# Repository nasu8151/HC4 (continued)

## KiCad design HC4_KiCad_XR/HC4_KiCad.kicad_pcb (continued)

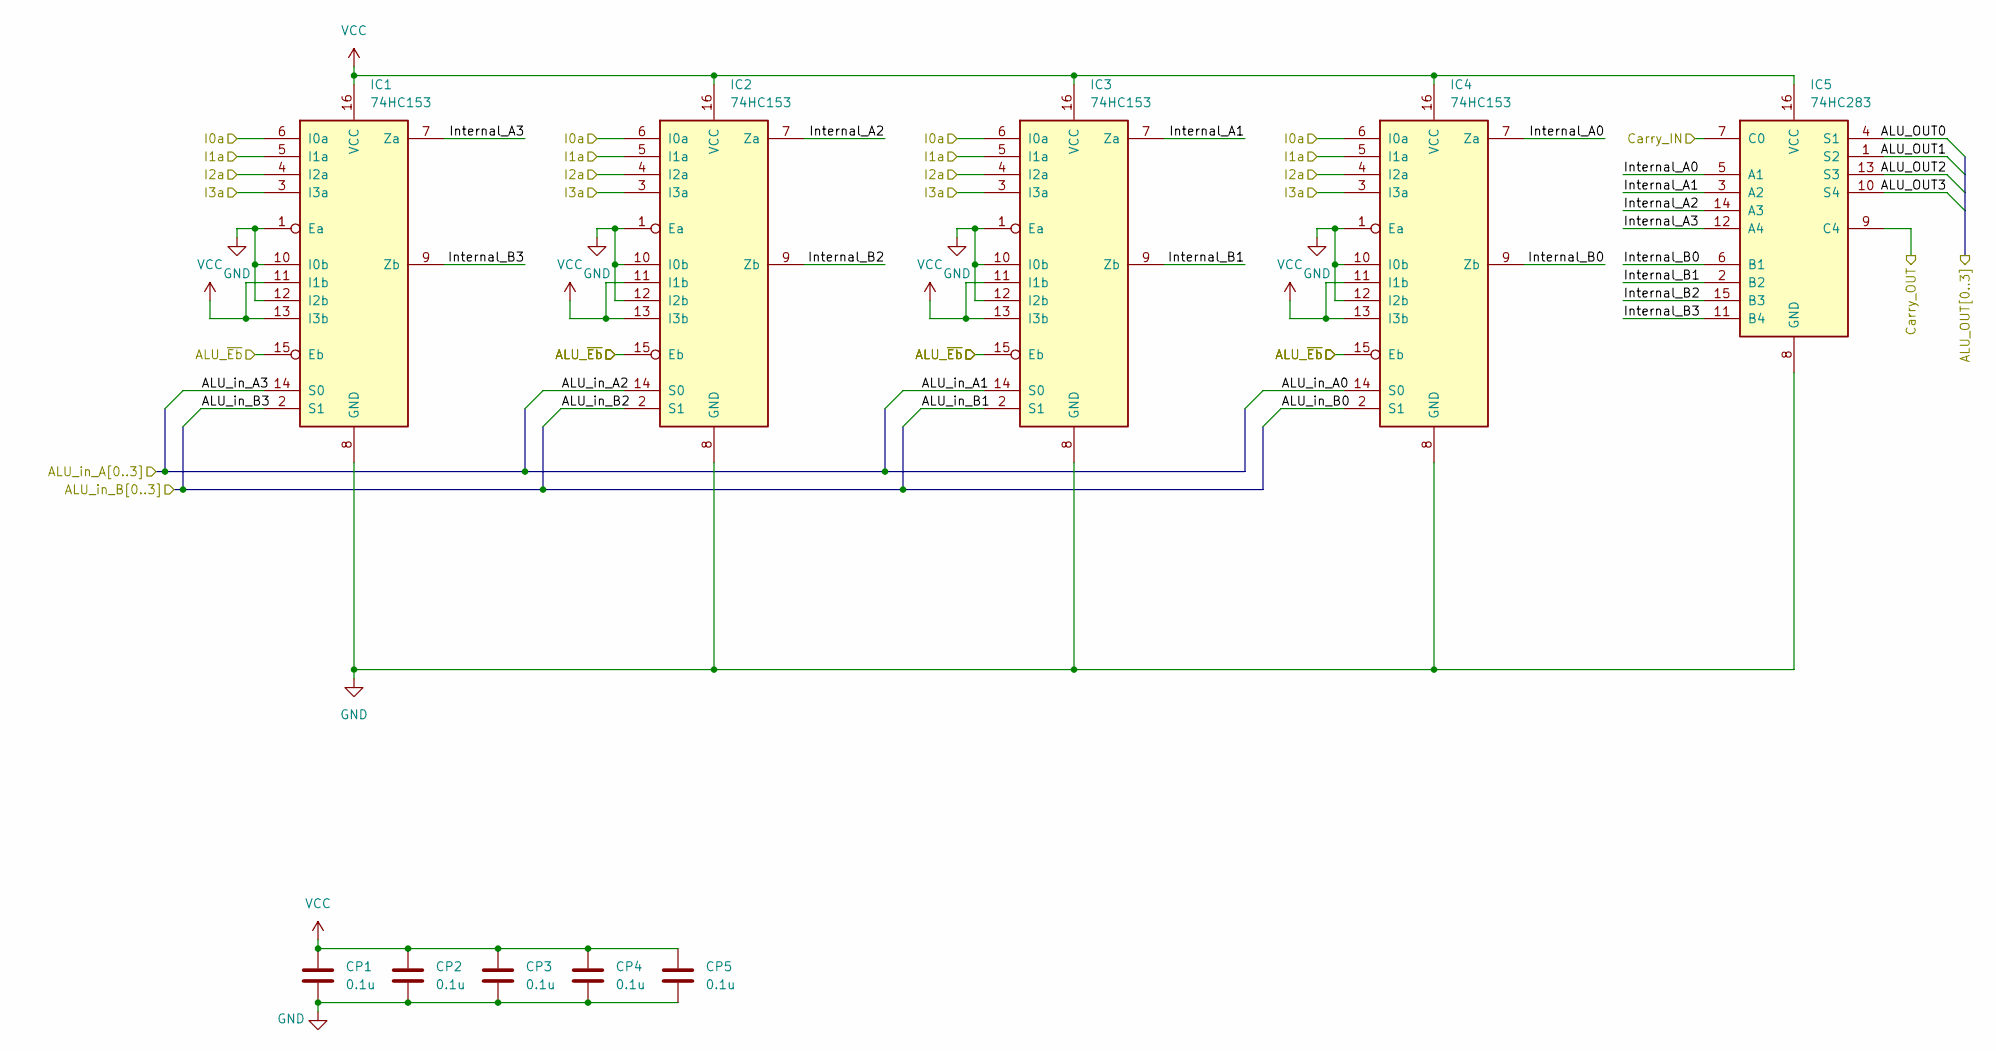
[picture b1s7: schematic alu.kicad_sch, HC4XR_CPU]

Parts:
CP1, CP2, CP3, CP4, CP5: 0.1u; C_0603_1608Metric
IC1, IC2, IC3, IC4: 74HC153; DIP-16_W7.62mm
IC5: 74HC283; DIP-16_W7.62mm

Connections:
/ALU/ALU_OUT0: IC5.4 (S1); also elsewhere on the board
/ALU/ALU_OUT1: IC5.1 (S2); also elsewhere on the board
/ALU/ALU_OUT2: IC5.13 (S3); also elsewhere on the board
/ALU/ALU_OUT3: IC5.10 (S4); also elsewhere on the board
/ALU/ALU_in_A0: IC4.14 (S0); also elsewhere on the board
/ALU/ALU_in_A1: IC3.14 (S0); also elsewhere on the board
/ALU/ALU_in_A2: IC2.14 (S0); also elsewhere on the board
/ALU/ALU_in_A3: IC1.14 (S0); also elsewhere on the board
/ALU/ALU_in_B0: IC4.2 (S1); also elsewhere on the board
/ALU/ALU_in_B1: IC3.2 (S1); also elsewhere on the board
/ALU/ALU_in_B2: IC2.2 (S1); also elsewhere on the board
/ALU/ALU_in_B3: IC1.2 (S1); also elsewhere on the board
/ALU/Carry_OUT: IC5.9 (C4); also elsewhere on the board
/ALU/I0a: IC1.6 (I0a), IC2.6 (I0a), IC3.6 (I0a), IC4.6 (I0a); also elsewhere on the board
/ALU/I1a: IC1.5 (I1a), IC2.5 (I1a), IC3.5 (I1a), IC4.5 (I1a); also elsewhere on the board
/ALU/I2a: IC1.4 (I2a), IC2.4 (I2a), IC3.4 (I2a), IC4.4 (I2a); also elsewhere on the board
/ALU/I3a: IC1.3 (I3a), IC2.3 (I3a), IC3.3 (I3a), IC4.3 (I3a); also elsewhere on the board
/ALU/Internal_A0: IC4.7 (Za), IC5.5 (A1)
/ALU/Internal_A1: IC3.7 (Za), IC5.3 (A2)
/ALU/Internal_A2: IC2.7 (Za), IC5.14 (A3)
/ALU/Internal_A3: IC1.7 (Za), IC5.12 (A4)
/ALU/Internal_B0: IC4.9 (Zb), IC5.6 (B1)
/ALU/Internal_B1: IC3.9 (Zb), IC5.2 (B2)
/ALU/Internal_B2: IC2.9 (Zb), IC5.15 (B3)
/ALU/Internal_B3: IC1.9 (Zb), IC5.11 (B4)
/Instruction Decoder/Carry_Flg: IC5.7 (C0); also elsewhere on the board
/Instruction Decoder/~Carry_EN: IC1.15 (Eb), IC2.15 (Eb), IC3.15 (Eb), IC4.15 (Eb); also elsewhere on the board
GND: CP1.2, CP2.2, CP3.2, CP4.2, CP5.2, IC1.1 (Ea), IC1.8 (GND), IC1.10 (I0b), IC1.12 (I2b), IC2.1 (Ea), IC2.8 (GND), IC2.10 (I0b), IC2.12 (I2b), IC3.1 (Ea), IC3.8 (GND), IC3.10 (I0b), IC3.12 (I2b), IC4.1 (Ea), IC4.8 (GND), IC4.10 (I0b), IC4.12 (I2b), IC5.8 (GND); also elsewhere on the board
VCC: CP1.1, CP2.1, CP3.1, CP4.1, CP5.1, IC1.11 (I1b), IC1.13 (I3b), IC1.16 (VCC), IC2.11 (I1b), IC2.13 (I3b), IC2.16 (VCC), IC3.11 (I1b), IC3.13 (I3b), IC3.16 (VCC), IC4.11 (I1b), IC4.13 (I3b), IC4.16 (VCC), IC5.16 (VCC); also elsewhere on the board

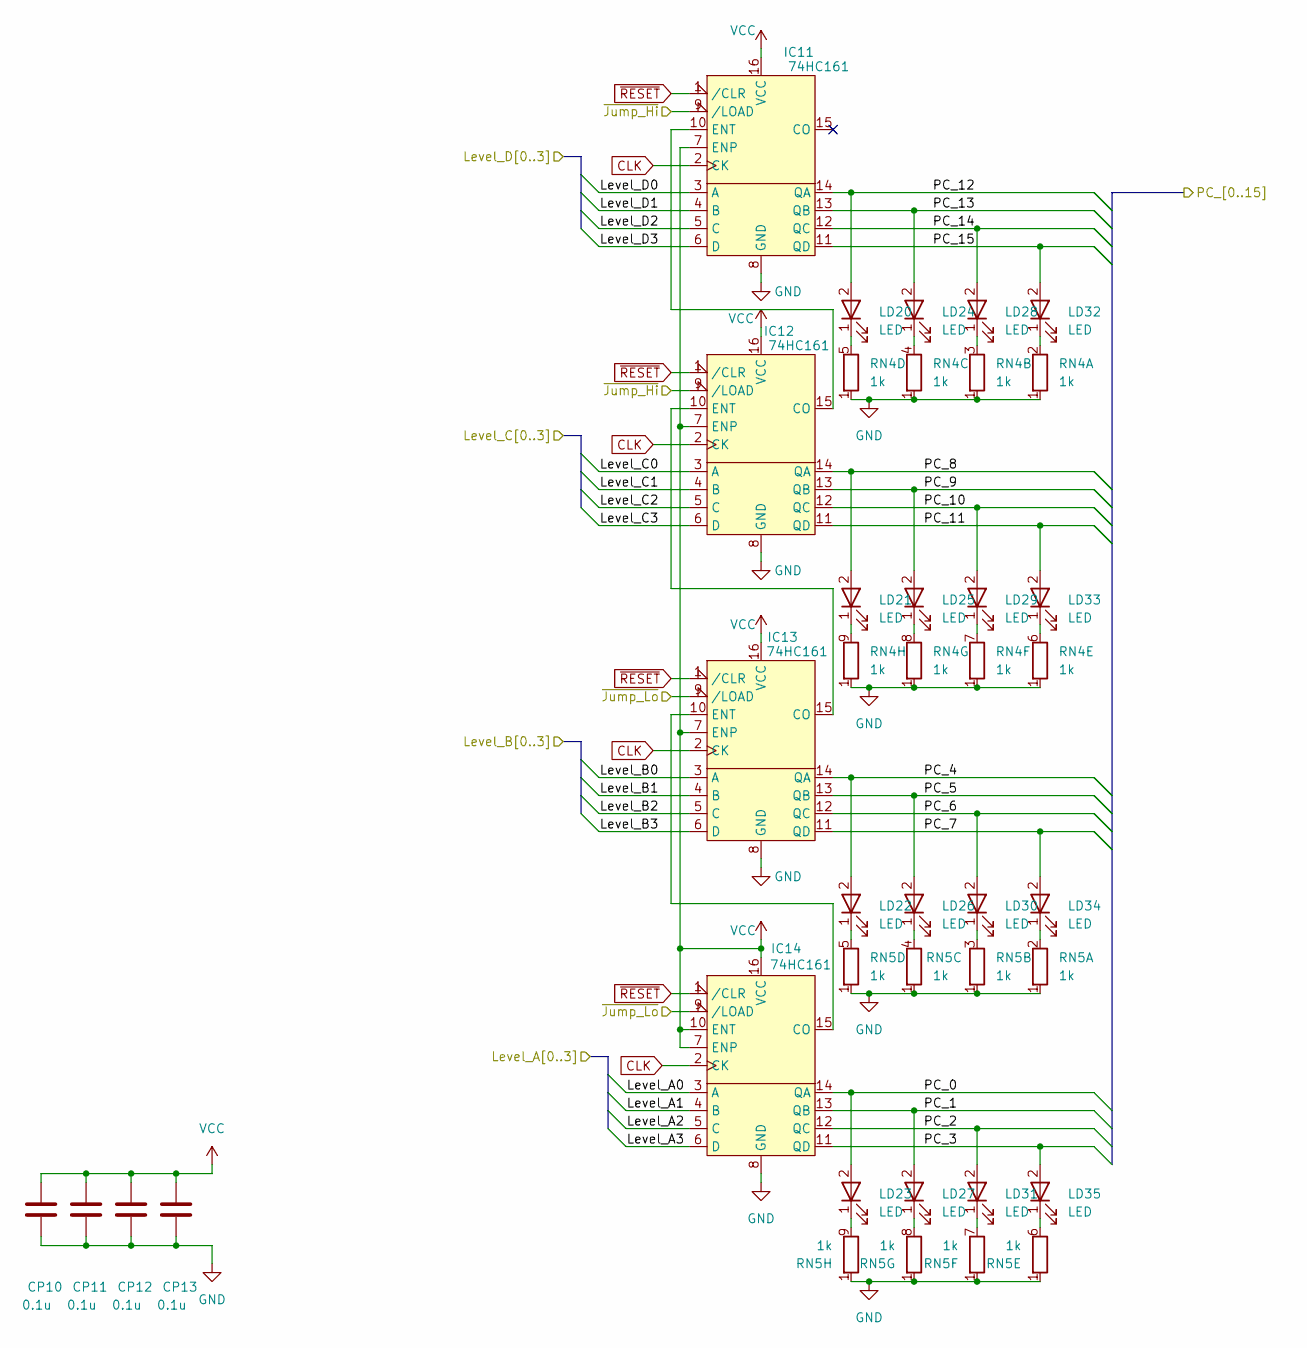
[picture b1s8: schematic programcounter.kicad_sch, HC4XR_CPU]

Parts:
CP10, CP11, CP12, CP13: 0.1u; C_0603_1608Metric
IC11, IC12, IC13, IC14: 74HC161; DIP-16_W7.62mm
LD20, LD21, LD22, LD23, LD24, LD25, LD26, LD27, LD28, LD29, LD30, LD31, LD32, LD33, LD34, LD35: LED; LED_Rectangular_W5.0mm_H2.0mm
RN4, RN5: 1k; R_Array_SIP9

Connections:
/ALU/ALU_in_A0: IC14.3 (A); also elsewhere on the board
/ALU/ALU_in_A1: IC14.4 (B); also elsewhere on the board
/ALU/ALU_in_A2: IC14.5 (C); also elsewhere on the board
/ALU/ALU_in_A3: IC14.6 (D); also elsewhere on the board
/ALU/ALU_in_B0: IC13.3 (A); also elsewhere on the board
/ALU/ALU_in_B1: IC13.4 (B); also elsewhere on the board
/ALU/ALU_in_B2: IC13.5 (C); also elsewhere on the board
/ALU/ALU_in_B3: IC13.6 (D); also elsewhere on the board
/Data BUS/Level_C0: IC12.3 (A); also elsewhere on the board
/Data BUS/Level_C1: IC12.4 (B); also elsewhere on the board
/Data BUS/Level_C2: IC12.5 (C); also elsewhere on the board
/Data BUS/Level_C3: IC12.6 (D); also elsewhere on the board
/Instruction Decoder/~Jump_Hi: IC13.9 (/LOAD), IC14.9 (/LOAD); also elsewhere on the board
/Instruction Decoder/~Jump_Lo: IC11.9 (/LOAD), IC12.9 (/LOAD); also elsewhere on the board
/Program Counter/Level_D0: IC11.3 (A); also elsewhere on the board
/Program Counter/Level_D1: IC11.4 (B); also elsewhere on the board
/Program Counter/Level_D2: IC11.5 (C); also elsewhere on the board
/Program Counter/Level_D3: IC11.6 (D); also elsewhere on the board
/Program Counter/PC_0: IC14.14 (QA), LD23.2; also elsewhere on the board
/Program Counter/PC_1: IC14.13 (QB), LD27.2; also elsewhere on the board
/Program Counter/PC_2: IC14.12 (QC), LD31.2; also elsewhere on the board
/Program Counter/PC_3: IC14.11 (QD), LD35.2; also elsewhere on the board
/Program Counter/PC_4: IC13.14 (QA), LD22.2; also elsewhere on the board
/Program Counter/PC_5: IC13.13 (QB), LD26.2; also elsewhere on the board
/Program Counter/PC_6: IC13.12 (QC), LD30.2; also elsewhere on the board
/Program Counter/PC_7: IC13.11 (QD), LD34.2; also elsewhere on the board
/Program Counter/PC_8: IC12.14 (QA), LD21.2; also elsewhere on the board
/Program Counter/PC_9: IC12.13 (QB), LD25.2; also elsewhere on the board
/Program Counter/PC_10: IC12.12 (QC), LD29.2; also elsewhere on the board
/Program Counter/PC_11: IC12.11 (QD), LD33.2; also elsewhere on the board
/Program Counter/PC_12: IC11.14 (QA), LD20.2; also elsewhere on the board
/Program Counter/PC_13: IC11.13 (QB), LD24.2; also elsewhere on the board
/Program Counter/PC_14: IC11.12 (QC), LD28.2; also elsewhere on the board
/Program Counter/PC_15: IC11.11 (QD), LD32.2; also elsewhere on the board
CLK: IC11.2 (CK), IC12.2 (CK), IC13.2 (CK), IC14.2 (CK); also elsewhere on the board
GND: CP10.2, CP11.2, CP12.2, CP13.2, IC11.8 (GND), IC12.8 (GND), IC13.8 (GND), IC14.8 (GND), RN4.1 (R1), RN5.1 (R1); also elsewhere on the board
unnamed: IC11.10 (ENT), IC12.15 (CO)
unnamed: IC12.10 (ENT), IC13.15 (CO)
unnamed: IC13.10 (ENT), IC14.15 (CO)
unnamed: LD20.1 (K_1), RN4.5 (R4.2)
unnamed: LD21.1 (K_1), RN4.9 (R8.2)
unnamed: LD22.1 (K_1), RN5.5 (R4.2)
unnamed: LD23.1 (K_1), RN5.9 (R8.2)
unnamed: LD24.1 (K_1), RN4.4 (R3.2)
unnamed: LD25.1 (K_1), RN4.8 (R7.2)
unnamed: LD26.1 (K_1), RN5.4 (R3.2)
unnamed: LD27.1 (K_1), RN5.8 (R7.2)
unnamed: LD28.1 (K_1), RN4.3 (R2.2)
unnamed: LD29.1 (K_1), RN4.7 (R6.2)
unnamed: LD30.1 (K_1), RN5.3 (R2.2)
unnamed: LD31.1 (K_1), RN5.7 (R6.2)
unnamed: LD32.1 (K_1), RN4.2 (R1.2)
unnamed: LD33.1 (K_1), RN4.6 (R5.2)
unnamed: LD34.1 (K_1), RN5.2 (R1.2)
unnamed: LD35.1 (K_1), RN5.6 (R5.2)
VCC: CP10.1, CP11.1, CP12.1, CP13.1, IC11.7 (ENP), IC11.16 (VCC), IC12.7 (ENP), IC12.16 (VCC), IC13.7 (ENP), IC13.16 (VCC), IC14.7 (ENP), IC14.10 (ENT), IC14.16 (VCC); also elsewhere on the board
~RESET: IC11.1 (/CLR), IC12.1 (/CLR), IC13.1 (/CLR), IC14.1 (/CLR); also elsewhere on the board

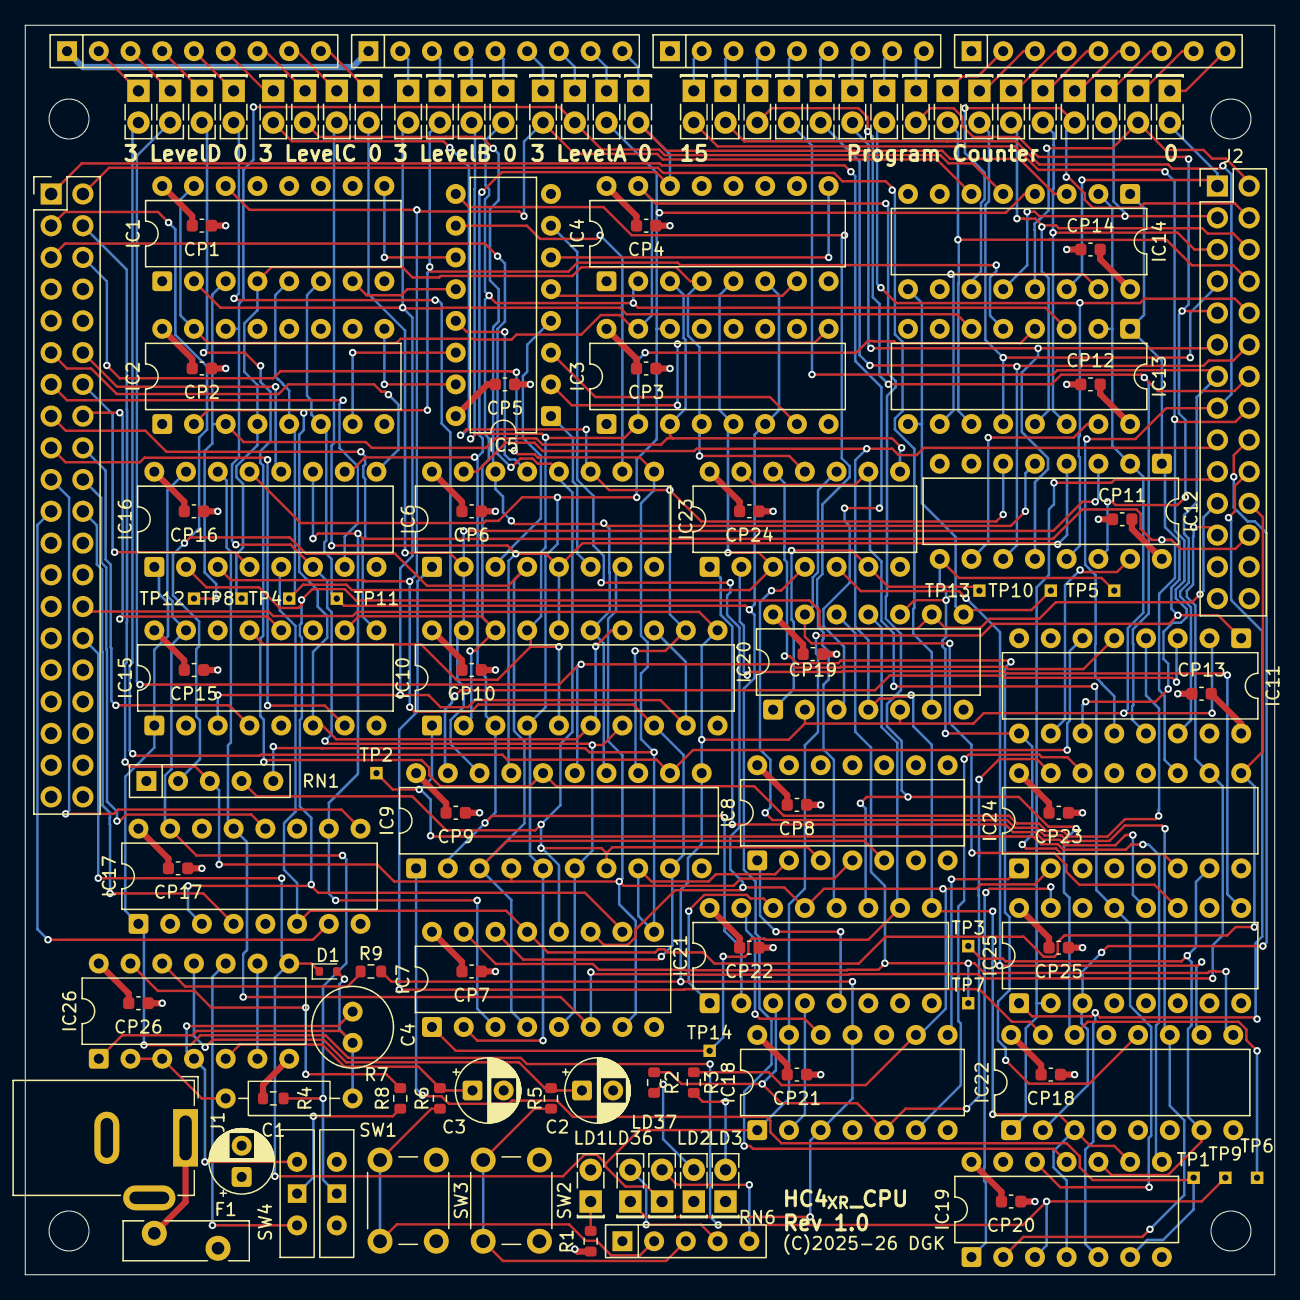
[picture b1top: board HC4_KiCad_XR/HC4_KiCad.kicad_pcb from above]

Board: 4 copper layers, 100.0 x 100.0 mm, 135 parts (0 on the bottom side), 160 nets.

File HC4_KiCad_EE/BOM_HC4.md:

| Value                       | Qty | Remarks                              |
| --------------------------- | --- | ------------------------------------ |
| Capacitor: 100u             | 1   |                                      |
| Capacitor: 10u              | 2   |                                      |
| Capacitor: 10u(Socket)      | 1   | Unipolar                             |
| Capacitor: 0.1u             | 24  |                                      |
| Zener: 5.6V                 | 1   |                                      |
| Diode: (1N4148 or equiv.)   | 40  |                                      |
| Polyfuse: 500mA             | 1   | For circuit protection               |
| RAM: (2716 ~ 27256)         | 1   |                                      |
| ROM: (6116~62256 or equiv.) | 1   | Write data hold time(tHD, tWHDX)=0ns |
| IC: 74HC153                 | 4   |                                      |
| IC: 74HC283                 | 1   |                                      |
| IC: 74HC257                 | 3   |                                      |
| IC: 74HC244                 | 1   |                                      |
| IC: 74HC4002                | 1   |                                      |
| IC: 74HC161                 | 4   |                                      |
| IC: 74HC377                 | 1   |                                      |
| IC: 74HC00                  | 1   |                                      |
| IC: 74HC32                  | 1   |                                      |
| IC: 74HC74                  | 1   |                                      |
| IC: 74HC4053                | 1   |                                      |
| IC: 74HC04                  | 1   |                                      |
| IC: 74HC151                 | 1   |                                      |
| IC: 74HC14                  | 1   |                                      |
| DC Jack                     | 1   |                                      |
| Pinheader: 01x01            | 1   |                                      |
| Pinheader: 02x20            | 1   |                                      |
| LED: 5mm                    | 1   |                                      |
| LED: Rectangle 2x3x4        | 26  |                                      |
| Resister: 1k                | 5   |                                      |
| Resister: 10k               | 4   |                                      |
| Resister: 100k              | 1   |                                      |
| Resister: 33k               | 1   |                                      |
| Resister: 100               | 2   |                                      |
| Resister array: 10k SIP5    | 1   |                                      |
| Resister array: 1k SIP5     | 3   |                                      |
| Resister array: 1k SIP9     | 3   |                                      |
| Resister array: 10k SIP9    | 1   |                                      |
| Slide SW_SPDT               | 3   |                                      |
| SW_Push                     | 2   |                                      |

[!Note]
* Please do not use mysterious Chinese parts.

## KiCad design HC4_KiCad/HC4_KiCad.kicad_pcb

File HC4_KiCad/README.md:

Schematics and board of HC4.

BOM:
[Bill of materials](https://github.com/nasu8151/HC4/blob/main/HC4_KiCad/BOM_HC4.md)

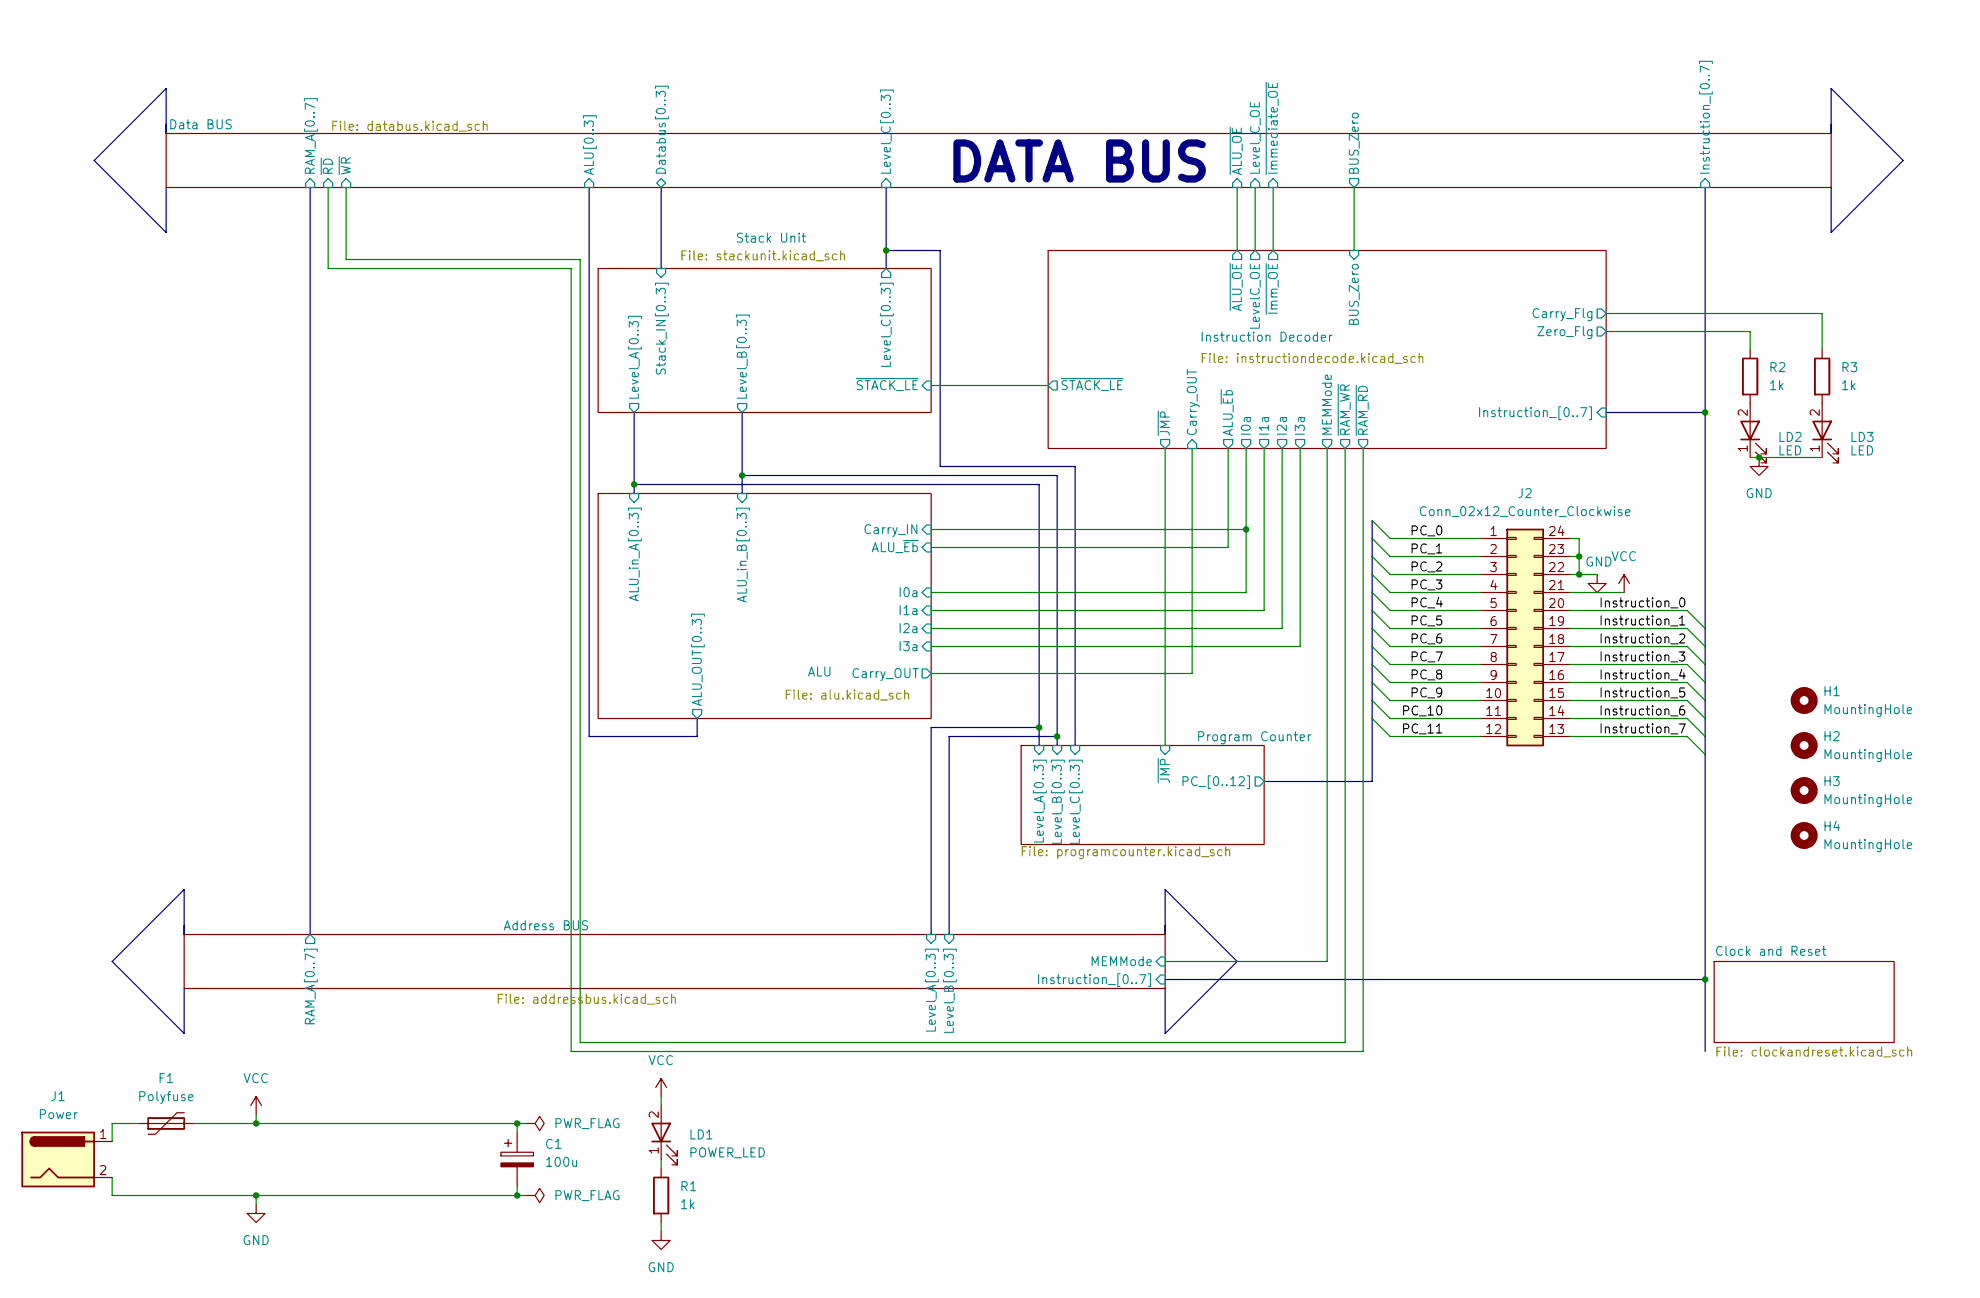
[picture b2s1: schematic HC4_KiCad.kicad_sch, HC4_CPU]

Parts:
C1: 100u; CP_Radial_D5.0mm_P2.50mm
F1: Polyfuse; Fuse_Bourns_MF-RG400
H1, H2, H3, H4: MountingHole; MountingHole_3.2mm_M3
J1: Power; BarrelJack_GCT_DCJ200-10-A_Horizontal
J2: Conn_02x12_Counter_Clockwise; PinHeader_2x12_P2.54mm_Vertical
LD1: POWER_LED; LED_Rectangular_W5.0mm_H2.0mm
LD2, LD3: LED; LED_Rectangular_W5.0mm_H2.0mm
R1, R2, R3: 1k; R_0603_1608Metric

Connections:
/Address BUS/Instruction_0: J2.20; also elsewhere on the board
/Address BUS/Instruction_1: J2.19; also elsewhere on the board
/Address BUS/Instruction_2: J2.18; also elsewhere on the board
/Address BUS/Instruction_3: J2.17; also elsewhere on the board
/Address BUS/Instruction_4: J2.16; also elsewhere on the board
/Address BUS/Instruction_5: J2.15; also elsewhere on the board
/Address BUS/Instruction_6: J2.14; also elsewhere on the board
/Address BUS/Instruction_7: J2.13; also elsewhere on the board
/Instruction Decoder/Carry_Flg: R3.1; also elsewhere on the board
/Instruction Decoder/Zero_Flg: R2.1; also elsewhere on the board
/Program Counter/PC_0: J2.1; also elsewhere on the board
/Program Counter/PC_1: J2.2; also elsewhere on the board
/Program Counter/PC_2: J2.3; also elsewhere on the board
/Program Counter/PC_3: J2.4; also elsewhere on the board
/Program Counter/PC_4: J2.5; also elsewhere on the board
/Program Counter/PC_5: J2.6; also elsewhere on the board
/Program Counter/PC_6: J2.7; also elsewhere on the board
/Program Counter/PC_7: J2.8; also elsewhere on the board
/Program Counter/PC_8: J2.9; also elsewhere on the board
/Program Counter/PC_9: J2.10; also elsewhere on the board
/Program Counter/PC_10: J2.11; also elsewhere on the board
/Program Counter/PC_11: J2.12; also elsewhere on the board
GND: C1.2, J1.2, J2.22, J2.23, J2.24, LD2.1 (K_1), LD3.1 (K_1), R1.2; also elsewhere on the board
unnamed: F1.1, J1.1
unnamed: LD1.1 (K_1), R1.1
unnamed: LD2.2, R2.2
unnamed: LD3.2, R3.2
VCC: C1.1, F1.2, J2.21, LD1.2; also elsewhere on the board

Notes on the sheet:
DATA BUS

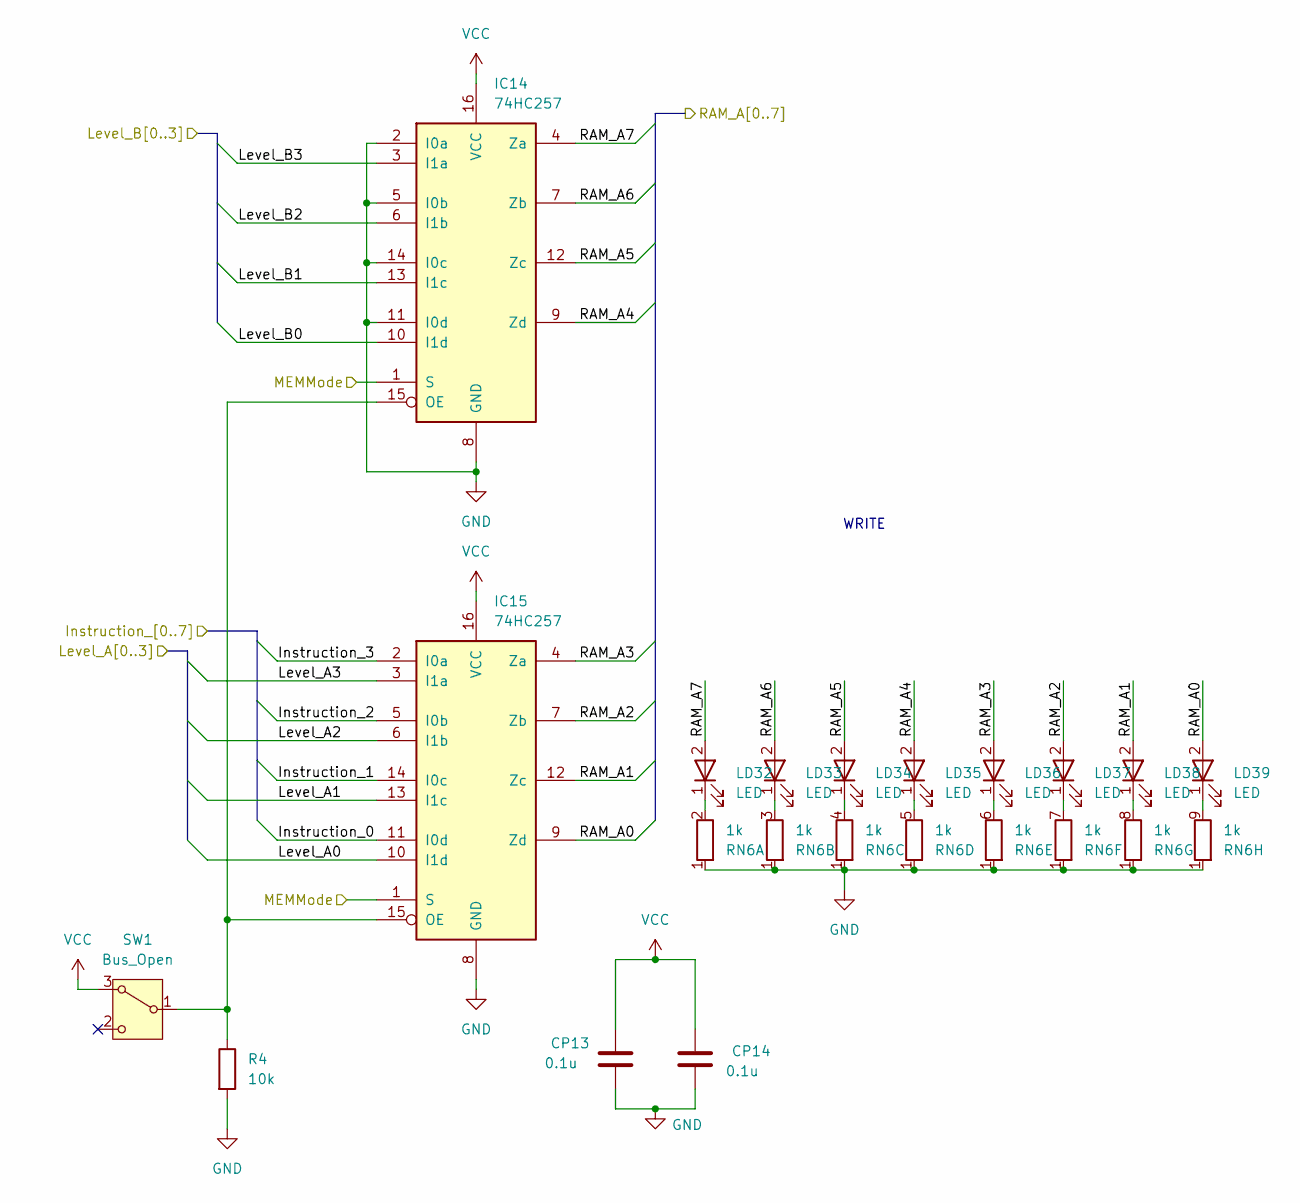
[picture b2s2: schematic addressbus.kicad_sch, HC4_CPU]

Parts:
CP13, CP14: 0.1u; C_0603_1608Metric
IC14, IC15: 74HC257; DIP-16_W7.62mm
LD32, LD33, LD34, LD35, LD36, LD37, LD38, LD39: LED; LED_Rectangular_W5.0mm_H2.0mm
R4: 10k; R_0603_1608Metric
RN6: 1k; R_Array_SIP9
SW1: Bus_Open; SW_Slide-03_Wuerth-WS-SLTV_10x2.5x6.4_P2.54mm

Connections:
/ALU/ALU_in_A0: IC15.10 (I1d); also elsewhere on the board
/ALU/ALU_in_A1: IC15.13 (I1c); also elsewhere on the board
/ALU/ALU_in_A2: IC15.6 (I1b); also elsewhere on the board
/ALU/ALU_in_A3: IC15.3 (I1a); also elsewhere on the board
/ALU/ALU_in_B0: IC14.10 (I1d); also elsewhere on the board
/ALU/ALU_in_B1: IC14.13 (I1c); also elsewhere on the board
/ALU/ALU_in_B2: IC14.6 (I1b); also elsewhere on the board
/ALU/ALU_in_B3: IC14.3 (I1a); also elsewhere on the board
/Address BUS/Instruction_0: IC15.11 (I0d); also elsewhere on the board
/Address BUS/Instruction_1: IC15.14 (I0c); also elsewhere on the board
/Address BUS/Instruction_2: IC15.5 (I0b); also elsewhere on the board
/Address BUS/Instruction_3: IC15.2 (I0a); also elsewhere on the board
/Address BUS/MEMMode: IC14.1 (S), IC15.1 (S); also elsewhere on the board
/Address BUS/RAM_A0: IC15.9 (Zd), LD39.2; also elsewhere on the board
/Address BUS/RAM_A1: IC15.12 (Zc), LD38.2; also elsewhere on the board
/Address BUS/RAM_A2: IC15.7 (Zb), LD37.2; also elsewhere on the board
/Address BUS/RAM_A3: IC15.4 (Za), LD36.2; also elsewhere on the board
/Address BUS/RAM_A4: IC14.9 (Zd), LD35.2; also elsewhere on the board
/Address BUS/RAM_A5: IC14.12 (Zc), LD34.2; also elsewhere on the board
/Address BUS/RAM_A6: IC14.7 (Zb), LD33.2; also elsewhere on the board
/Address BUS/RAM_A7: IC14.4 (Za), LD32.2; also elsewhere on the board
GND: CP13.2, CP14.2, IC14.2 (I0a), IC14.5 (I0b), IC14.8 (GND), IC14.11 (I0d), IC14.14 (I0c), IC15.8 (GND), R4.2, RN6.1 (R1); also elsewhere on the board
unnamed: IC14.15 (OE), IC15.15 (OE), R4.1, SW1.1 (B)
unnamed: LD32.1 (K_1), RN6.2 (R1.2)
unnamed: LD33.1 (K_1), RN6.3 (R2.2)
unnamed: LD34.1 (K_1), RN6.4 (R3.2)
unnamed: LD35.1 (K_1), RN6.5 (R4.2)
unnamed: LD36.1 (K_1), RN6.6 (R5.2)
unnamed: LD37.1 (K_1), RN6.7 (R6.2)
unnamed: LD38.1 (K_1), RN6.8 (R7.2)
unnamed: LD39.1 (K_1), RN6.9 (R8.2)
VCC: CP13.1, CP14.1, IC14.16 (VCC), IC15.16 (VCC), SW1.3 (A); also elsewhere on the board

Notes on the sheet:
WRITE
